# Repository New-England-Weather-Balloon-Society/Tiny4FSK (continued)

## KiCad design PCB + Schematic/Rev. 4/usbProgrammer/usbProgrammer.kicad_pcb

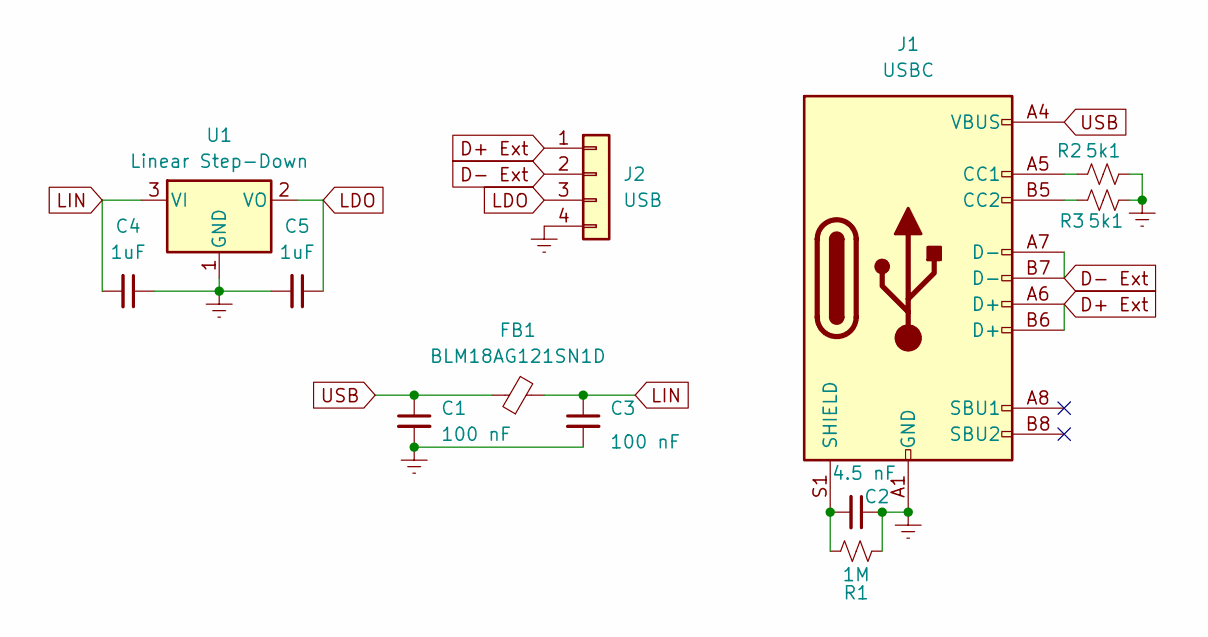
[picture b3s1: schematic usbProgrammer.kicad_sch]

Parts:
C1, C3: 100 nF; C_0805_2012Metric_Pad1.18x1.45mm_HandSolder
C2: 4.5 nF; C_0805_2012Metric_Pad1.18x1.45mm_HandSolder
C4, C5: 1uF; C_0805_2012Metric_Pad1.18x1.45mm_HandSolder
FB1: BLM18AG121SN1D; R_0603_1608Metric_Pad0.98x0.95mm_HandSolder
J1: USBC; USB_C_Receptacle_GCT_USB4105-xx-A_16P_TopMnt_Horizontal
J2: USB; PinHeader_1x04_P2.54mm_Vertical
R1: 1M; R_0805_2012Metric_Pad1.20x1.40mm_HandSolder
R2, R3: 5k1; R_0805_2012Metric_Pad1.20x1.40mm_HandSolder
U1: Linear Step-Down; MCP1700

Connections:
D+ Ext: J1.A6 (D+), J1.B6 (D+), J2.1
D- Ext: J1.A7 (D-), J1.B7 (D-), J2.2
Earth: C1.2, C2.1, C3.2, C4.1, C5.2, J1.A1 (GND), J1.A12 (GND), J1.B1 (GND), J1.B12 (GND), J2.4, R1.2, R2.1, R3.1, U1.1 (GND)
LDO: C5.1, J2.3, U1.2 (VO)
LIN: C3.1, C4.2, FB1.2, U1.3 (VI)
unnamed: J1.A5 (CC1), R2.2
unnamed: J1.B5 (CC2), R3.2
unnamed: C2.2, J1.S1 (SHIELD), R1.1
USB: C1.1, FB1.1, J1.A4 (VBUS), J1.A9 (VBUS), J1.B4 (VBUS), J1.B9 (VBUS)

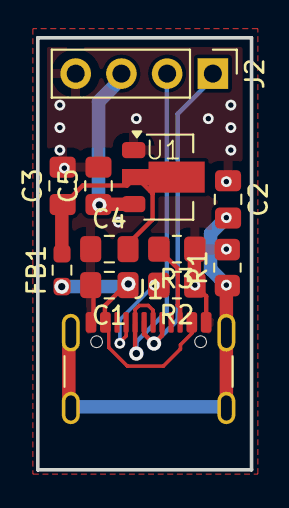
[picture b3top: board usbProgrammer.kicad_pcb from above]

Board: 4 copper layers, 11.9 x 24.0 mm, 12 parts (0 on the bottom side), 9 nets.

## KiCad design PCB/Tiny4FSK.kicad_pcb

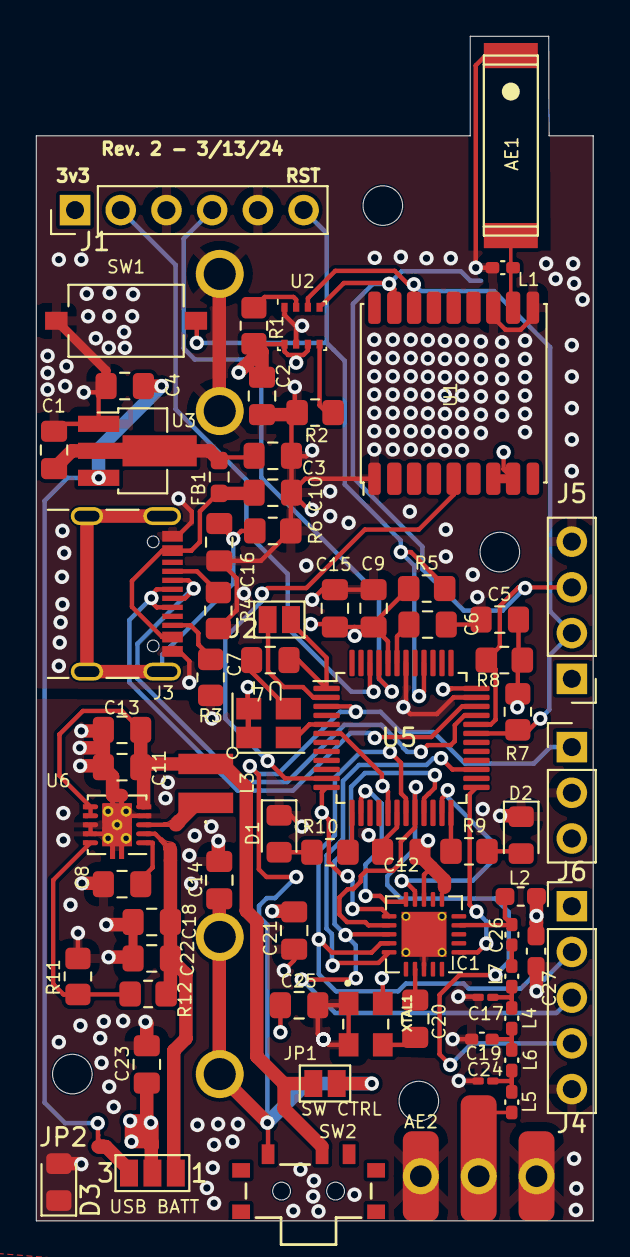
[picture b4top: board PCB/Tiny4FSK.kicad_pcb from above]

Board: 4 copper layers, 30.9 x 65.8 mm, 75 parts (1 on the bottom side), 49 nets.

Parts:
AE1: GPS ANT; GPS1003
AE2: ANT; Antenna_Whip
BT1: AAA; BAT_BK-82
C1, C2, C4, C6, C14, C23: 1uF; C_0805_2012Metric_Pad1.18x1.45mm_HandSolder
C3, C10: 100 nF (J1); C_0805_2012Metric_Pad1.18x1.45mm_HandSolder
C5, C8, C9, C11, C15, C21, C22: 100nF; C_0805_2012Metric_Pad1.18x1.45mm_HandSolder
C7, C20: 100 pF; C_0805_2012Metric_Pad1.18x1.45mm_HandSolder
C12, C13: 10uF; C_0805_2012Metric_Pad1.18x1.45mm_HandSolder
C16: 4.5 nF; C_0805_2012Metric_Pad1.18x1.45mm_HandSolder
C17: 15 pF; C_0201_0603Metric_Pad0.64x0.40mm_HandSolder
C18: 22uF; C_0805_2012Metric_Pad1.18x1.45mm_HandSolder
C19: 12 pF; C_0402_1005Metric_Pad0.74x0.62mm_HandSolder
C24: 10 pF; C_0201_0603Metric_Pad0.64x0.40mm_HandSolder
C25: 10 nF; C_0805_2012Metric_Pad1.18x1.45mm_HandSolder
C26: 9.1 pF; C_0402_1005Metric_Pad0.74x0.62mm_HandSolder
C27: 100nF; C_0603_1608Metric_Pad1.08x0.95mm_HandSolder
D1: Success; LED_0805_2012Metric_Pad1.15x1.40mm_HandSolder
D2: Error; LED_0805_2012Metric_Pad1.15x1.40mm_HandSolder
D3: Power; LED_0805_2012Metric_Pad1.15x1.40mm_HandSolder
FB1: BLM18AG121SN1D (J1); R_0603_1608Metric_Pad0.98x0.95mm_HandSolder
H1, H2, H3, H4: MountingHole; MountingHole_2.2mm_M2
IC1: SI4063; QFN-20-1EP_4x4mm_P0.5mm_EP2.5x2.5mm_ThermalVias
J1: SWD; PinHeader_1x06_P2.54mm_Vertical
J2: OPTIONAL; SolderJumper-2_P1.3mm_Open_Pad1.0x1.5mm
J3: USBC; USB_C_Receptacle_GCT_USB4105-xx-A_16P_TopMnt_Horizontal
J4: SPI; PinHeader_1x05_P2.54mm_Vertical
J5: I2C; PinHeader_1x04_P2.54mm_Vertical
J6: Power; PinHeader_1x03_P2.54mm_Vertical
JP1: SWITCH_EN; SolderJumper-2_P1.3mm_Open_Pad1.0x1.5mm
JP2: Source; SolderJumper-3_P1.3mm_Open_Pad1.0x1.5mm_NumberLabels
L1, L7: 33 nH; L_0402_1005Metric_Pad0.77x0.64mm_HandSolder
L2: 220 nH; L_0603_1608Metric_Pad1.05x0.95mm_HandSolder
L3: 2.2uH; LPS3015222MRB
L4: 30 nH; L_0402_1005Metric_Pad0.77x0.64mm_HandSolder
L5: 22 nH; L_0402_1005Metric_Pad0.77x0.64mm_HandSolder
L6: 36 nH; L_0402_1005Metric_Pad0.77x0.64mm_HandSolder
R1, R2: 10k; R_0805_2012Metric_Pad1.20x1.40mm_HandSolder
R3, R4: 5k1; R_0805_2012Metric_Pad1.20x1.40mm_HandSolder
R5: 220; R_0805_2012Metric_Pad1.20x1.40mm_HandSolder
R6: 1M; R_0805_2012Metric_Pad1.20x1.40mm_HandSolder
R7, R8: 1.8k; R_0805_2012Metric_Pad1.20x1.40mm_HandSolder
R9, R10: 100; R_0805_2012Metric_Pad1.20x1.40mm_HandSolder
R11: 900k; R_0805_2012Metric_Pad1.20x1.40mm_HandSolder
R12: 5M; R_0805_2012Metric_Pad1.20x1.40mm_HandSolder
SW1: RST; SW_Tactile_SPST_NO_Straight_CK_PTS636Sx25SMTRLFS
SW2: BATT PWR; WS-SLSU_6p7x2p7_WRE
U1: MAX-M10S; ublox_MAX
U2: BME280; Bosch_LGA-8_2.5x2.5mm_P0.65mm_ClockwisePinNumbering
U3: Linear Step-Down; SOT-89-3_Handsoldering
U4: TCXO MCU; ATXK-H11-E-32.768KHZ-E50-T3
U5: ATSAMD21G18A-A; TQFP-48_7x7mm_P0.5mm
U6: TPS61200DRC; Texas_S-PVSON-N10_ThermalVias
XTAL1: OSC_ECS-TXO-32CSMV-260-AN-TR

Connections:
+3.3V: C2.1, C5.1, C9.2, C12.1, C15.1, C21.1, C23.1, C25.2, C27.2, D3.2 (A), IC1.6 (VDD_1), IC1.8 (VDD_2), J1.1, J4.1, J5.1, J6.3, JP2.2 (C), L2.1, R1.1, R5.2, R7.2, R8.2, U1.7 (VCC_IO), U1.8 (VCC), U2.6 (VDDIO), U2.8 (VDD), U4.1 (EN), U4.4 (VDD), U5.6 (VDDANA), U5.17 (VDDIO), U5.36 (VDDIO), U5.44 (VDDIN), XTAL1.4 (VDD)
ANT_GPS: AE1.2 (PCB_Trace), L1.2, U1.11 (RF_IN)
BATT_SENSE: BT1.+, C14.1, J6.1, JP1.2 (B), SW2.1 (A), U5.3 (PA02)
BOOST: C18.1, C22.1, JP2.1 (A), R12.1, U6.2 (VOUT)
BST_IN: C11.1, C13.1, JP1.1 (A), L3.2, SW2.2 (B), U6.5 (VIN), U6.6 (EN), U6.7 (UVLO)
D+: J3.A6 (D+), J3.B6 (D+), U5.34 (PA25)
D-: J3.A7 (D-), J3.B7 (D-), U5.33 (PA24)
ERROR: R9.1, U5.24 (PA15)
EXTINT: U1.5 (EXTINT), U5.11 (PA06)
Earth: AE1.1 (FEED), AE2.2 (Shield), BT1.-, C1.1, C2.2, C3.2, C4.2, C5.2, C6.2, C8.2, C9.1, C10.2, C11.2, C12.2, C13.2, C14.2, C15.2, C16.1, C17.2, C18.2, C19.2, C21.2, C22.2, C23.2, C24.2, C25.1, C27.1, D1.1 (K), D2.1 (K), D3.1 (K), IC1.18 (GND_1), IC1.21 (GND_2), J1.3, J1.5, J3.A1 (GND), J3.A12 (GND), J3.B1 (GND), J3.B12 (GND), J4.5, J5.4, J6.2, L1.1, R2.2, R3.1, R4.1, R6.2, R11.2, SW1.1, U1.1 (GND), U1.10 (GND), U1.12 (GND), U2.1 (GND), U2.7 (GND), U3.1 (GND), U4.2 (GND), U5.5 (GNDANA), U5.18 (GND), U5.35 (GND), U5.42 (GND), U6.4 (PGND), U6.8 (PS), U6.9 (GND), U6.11 (PAD), XTAL1.1 (GND), XTAL1.2 (GND)
GPIO0: IC1.9 (GPIO0), U5.23 (PA14)
GPIO1: IC1.10 (GPIO1), U5.14 (PA09)
LDO: C4.1, JP2.3 (B), U3.3 (VI)
LIN: C1.2, C3.1, FB1.2, U3.2 (VO)
MISO: IC1.13 (SDO), J4.3, U5.21 (PA12)
MOSI: IC1.14 (SDI), J4.2, U5.19 (PB10)
unnamed: AE2.1 (RF), L5.2
unnamed: C17.1, L4.1, L7.2
unnamed: C19.1, L4.2, L6.1
unnamed: C24.1, L5.1, L6.2
unnamed: C26.2, L7.1
unnamed: D1.2 (A), R10.1
unnamed: D2.2 (A), R9.2
unnamed: C20.2, IC1.17 (XIN)
unnamed: J3.A5 (CC1), R4.2
unnamed: J3.B5 (CC2), R3.2
unnamed: C16.2, J3.S1 (SHIELD), R6.1
unnamed: R1.2, U2.2 (CSB)
unnamed: R2.1, U2.5 (SDO)
unnamed: C7.2, U4.3 (OUTPUT)
unnamed: C6.1, U5.43 (VDDCORE)
unnamed: R11.1, R12.2, U6.10 (FB)
unnamed: L3.1, U6.3 (L)
unnamed: C8.1, U6.1 (VAUX)
OPT XOUT: J2.2, U5.2 (PA01)
RF_ANT: C26.1, IC1.4 (TX), L2.2
RF_RST: IC1.11 (NIRQ), U5.12 (PA07)
RF_SS: IC1.15 (NSEL), U5.27 (PA18)
RF_XO: C20.1, XTAL1.3 (CLK_OUT)
SCK: IC1.12 (SCLK), J4.4, U5.20 (PB11)
SCL: J5.3, R8.1, U1.17 (SCL), U2.4 (SCK), U5.32 (PA23)
SDA: J5.2, R7.1, U1.16 (SDA), U2.3 (SDI), U5.31 (PA22)
SDN: IC1.1 (SDN), U5.25 (PA16)
SUCCESS: R10.2, U5.13 (PA08)
SWCLK: J1.4, U5.45 (PA30)
SWDIO: J1.2, U5.46 (PA31)
TCXO: C7.1, J2.1, U5.1 (PA00)
USB: C10.1, FB1.1, J3.A4 (VBUS), J3.A9 (VBUS), J3.B4 (VBUS), J3.B9 (VBUS)
nRST: J1.6, R5.1, SW1.2, U5.40 (~RESET)

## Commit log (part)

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2021-09-12 Add link to payload ID list
2023-09-30 Rename horusbinary_radiolib.ino to Tiny4FSK.ino
2023-11-19 Create a
2023-11-19 Rename File
2023-11-25 Create LICENSE
2023-12-10 GPS Sleep Mode
2023-12-13 Setup for VS Code integration
2023-12-14 Code Formatting
2023-12-29 Code Refactoring
    Big Push for Somewhat-Useable Code. But don't use it yet!
2023-12-29 More Refactoring!
    MCU Sleep Modes, Beautifcation, Config Options.
2024-01-13 experimental voltage reading
2024-02-04 Added JTAG Pinout description
2024-02-04 Rename JTAG_Pinout.png to images/JTAG_Pinout.png
2024-02-09 Logo Upload
2024-02-09 Add first doc draft
2024-02-09 Rename Tiny4FSK.kicad_pro to PCB/Tiny4FSK.kicad_pro
2024-02-14 Update Tiny4FSK.ino with I2C scanning
2024-02-20 Update LICENSE
2024-06-13 #pragma once updates
2024-06-26 CW Callsign Identification, Code Cleanup, Pragma Once
2024-06-26 New sanity check option
2024-06-26 Comments formatting
2024-06-26 tweaks
2024-06-27 GPL v3 and rename SOFTWARE-MEDIA-LICENSE to SOFTWARE-DOCS-LICENSE
2024-06-27 Update HARDWARE-LICENSE
2024-06-27 Rename HARDWARE-LICENSE to LICENSE.OHL
2024-06-27 Rename SOFTWARE-DOCS-LICENSE to LICENSE.GPL
2024-06-27 Rename LICENSE.GPL to LICENSE-SOFTWARE-DOCS
2024-06-27 Rename LICENSE.OHL to LICENSE-HARDWARE
2024-06-27 Rehaul Repo Structure
2024-06-27 licensing changes
2024-07-02 Rev. 4 PCB Files
2024-07-03 Add ATGM336H, start snap-off boards
2024-07-04 USB Breakout, PCB further along
2024-07-04 Expansion GPIO
2024-07-04 USB Breakout
2024-07-05 USB Prog, updates
2024-07-06 0402s for JLCPCB capabilities
2024-07-10 Finish USB breakout
2024-07-10 Make DRC happy
2024-07-15 JLCPCB part numbering, PCB updates
2024-07-15 Smaller footprints, resize board
2024-07-16 New cheaper parts
2024-07-16 More cheaper components (even more!)
2024-07-16 Inductors
2024-07-16 Update PCB, add more jlcpcb parts
2024-07-16 Neaten up schematic, add breakaway tabs and stitching vias
2024-07-16 Gerbers, stitching, SLP
2024-07-16 Fix breakaway, mounting holes
2024-07-16 Neaten up reference designators
2024-07-17 Reference designators
2024-07-17 More reference designators
2024-07-17 USB, 3D models, Reference Designators
2024-07-17 FAB output, USB
2024-07-17 JLCPCB optimization
2024-07-18 Better Breakaway tabs, JLC export
2024-07-18 JLCPCB Centroid Fixes
2024-07-18 Silkscreen, Pricing
2024-07-18 JLCPCB export, Silkscreen
2024-07-18 LNA Add-On, Silkscreen
2024-07-19 LNA Addon, JLC Parts
2024-07-19 LNA, JLCPCB
2024-07-27 quick fixes
2024-07-29 Custom Field List Update
2024-10-04 Better Pictures
2024-11-04 PCB Layout, RF Matching
2024-11-04 Revert "PCB Layout, RF Matching"
    This reverts commit 01f3e4a1f70094b95dbec544faeab450dc2c770a.
2024-11-11 Matching on GPS, modifications
2024-11-11 Finished?
2024-11-16 Sponsorship
2024-11-16 3d models
2024-11-16 design review updates
    Minor changes following design review
2024-12-21 new gps module (in dev)
2024-12-21 Rebase Rev. 4 PCB files
2024-12-21 config update
2024-12-21 reset config
2024-12-21 Solve custom field list issues
2024-12-21 actually fix field list
2024-12-22 code cleanup
2024-12-22 status update, pcbway sponsorship section
2024-12-22 add default config.h
2024-12-22 Use threading to update GPS values
2024-12-22 use thrwading to update gps values
2024-12-22 update readme and neaten up code
2024-12-22 start of sd card logging
2024-12-23 licensing
2024-12-23 restructure header files, add utils headers
2024-12-29 clean out sd code, adjust voltage formula
2024-12-31 updae readme with new pcb pics
2025-01-04 revert kicad version to 8
2025-01-04 update 3d model paths
2025-01-17 increase battery spacing, revamp silkscreen
2025-01-19 small updates to PCB, revamp README
2025-01-19 README update
2025-01-19 add antenna theory
2025-01-19 minor readme updates
2025-01-20 more assorted readme improvements
2025-02-07 Make PCB more production-friendly
2025-02-07 setting update
2025-03-22 small updates
2025-05-20 Refactor Tiny4FSK project files and add shield functionality
    - Updated Tiny4FSK.kicad_pro to include layer_pairs and changed the 3D model reference to Tiny4FSK-simple.step.
    - Modified Tiny4FSK.kicad_sch to replace a 7-pin connector with a 9-pin connector, adjusting pin positions and properties accordingly.
    - Introduced new shield.cpp and shield.h files to support interaction with the Tiny4FSK General Shield, including I2C scanning and initialization for BME280, IMU, and OLED devices.
    - Added a new 3D model file Tiny4FSK-simple.step.
2025-05-30 new production files
2025-07-05 implement new IMU, OLED, and SD card functionalities. Added font and utility functions for display management.
2025-07-10 allow it to work with no sd card connected
2025-07-21 stable!
2025-07-30 add some more flight data
2026-01-02 enable automatic imu initialization
2026-01-02 add counterpoise to pcb
2026-01-02 code formatting + enable bme initialization
2026-01-02 remove imu capabilities (new breakout board with new module coming soon)
2026-01-02 happy new years!
2026-01-02 add imu testing code to gitignore
2026-02-06 much better pics
2026-03-22 kicad 10!
2026-04-11 super duper early v3 testing
2026-04-17 move clamping and clamp all values
2026-04-17 correct millivolts formatting
2026-04-21 documentation updates
2026-04-21 fix code comments
2026-04-21 usb not needed
2026-04-21 new picture
2026-04-21 remove unused function
2026-04-21 remove kicad artifacts
2026-04-21 clean up prod files
2026-04-21 polish readme
2026-04-24 make callsign handling more robust (allows suffixes!)
2026-04-26 new receiver
2026-04-26 specify battery life
2026-05-06 tad bit lower power
2026-05-06 new batch pcb
2026-05-07 easier setup
2026-05-14 battery life
2026-05-14 clarification
2026-05-23 typo and disclaimer
2026-05-25 output power levels
2026-06-26 clearer battery
2026-06-26 better comments
